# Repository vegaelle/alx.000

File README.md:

# ALX.000

ALX.000 is a compact 18-keys computer numpad, powered by a Seeed XIAO RP2040
micro-controller, and ultra-low-profile Kailh "X" PG1316S switches. It runs QMK,
although support for RMK may come later.

## What’s included here?

This repository contains all needed files for building the keyboard, including parts
list, assembly instructions and useful links.

- The [alx-000.json](alx-000.json) represents the keyboard shape,
produced by [Keyboard-Layout-Editor](https://www.keyboard-layout-editor.com/##@_name=ALX.000&author=vegaelle%3B&@_x:1.5&t=%23ff0000&a:7%3B&=%E2%86%90&_t=%230000ff%3B&=%E2%86%92%3B&@_y:0.5&t=%23000000%0A%23ff0000&a:4%3B&=%0AHome%0A%0A%0A%0A%0A%0A%0A%0A7&=%0A%E2%86%91%0A%0A%0A%0A%0A%0A%0A%0A8&=%0APgUp%0A%0A%0A%0A%0A%0A%0A%0A9&_x:0.5%3B&=%0A,%0A%0A%0A%0A%0A%0A%0A%0A%2F%2F%3B&@=%0A%E2%86%90%0A%0A%0A%0A%0A%0A%0A%0A4&_t=%23000000&a:7&n:true%3B&=5&_t=%23000000%0A%23ff0000&a:4%3B&=%0A%E2%86%92%0A%0A%0A%0A%0A%0A%0A%0A6&_x:0.5%3B&=%0A%2F=%0A%0A%0A%0A%0A%0A%0A%0A*%3B&@=%0AEnd%0A%0A%0A%0A%0A%0A%0A%0A1&=%0A%E2%86%93%0A%0A%0A%0A%0A%0A%0A%0A2&=%0APgDn%0A%0A%0A%0A%0A%0A%0A%0A3&_x:0.5%3B&=%0A%3F%0A%0A%0A%0A%0A%0A%0A%0A-%3B&@=%0ABack%0A%0A%0A%0A%0A%0A%0A%0AEnt&=%0AIns%0A%0A%0A%0A%0A%0A%0A%0A0&=%0ADel%0A%0A%0A%0A%0A%0A%0A%0A.&_x:0.5%3B&=%0A%3F%0A%0A%0A%0A%0A%0A%0A%0A+)
- The [kicad](kicad/) directory contains the Kicad project, representing the PCB. It
uses [Scottokeebs](https://github.com/joe-scotto/scottokeebs/tree/main/Extras/ScottoKicad) libraries and [Mikefive](https://github.com/mikeholscher/zmk-config-mikefive/tree/main/files)’s footprints
- the PG1316 keycaps can be 3D-printed, either with the [blank model](pg1316s_keycap.3mf), or with the OpenSCAD script that allows customization, even with labels, in the [keycaps](keycaps) directory
- The case has been designed in [OnShape](https://cad.onshape.com/documents/826440f605c19707b80cd65a/w/c0d96e8d9f2b88321da9ff87/e/a88972e39d45dd27abd71d1e?renderMode=0&uiState=67a777fa368aed7a59f7b05c). I would have liked to make it in FreeCAD but even in 1.0, it simply wasn’t usable enough.
- The [qmk_firmware/keyoards/alx/000](qmk_firmware/keyboards/alx/000) directory contains
the keyboard definition for QMK, required to build the firmware and edit the keymap.

## Why design a numpad in the first place?

1. Because it’s fun
2. I ultimately want to design my own ergomech keyboard, and this simple project is a
   first step
3. I wanted to try those ultra-thin switches, and it will be a nice way to try those

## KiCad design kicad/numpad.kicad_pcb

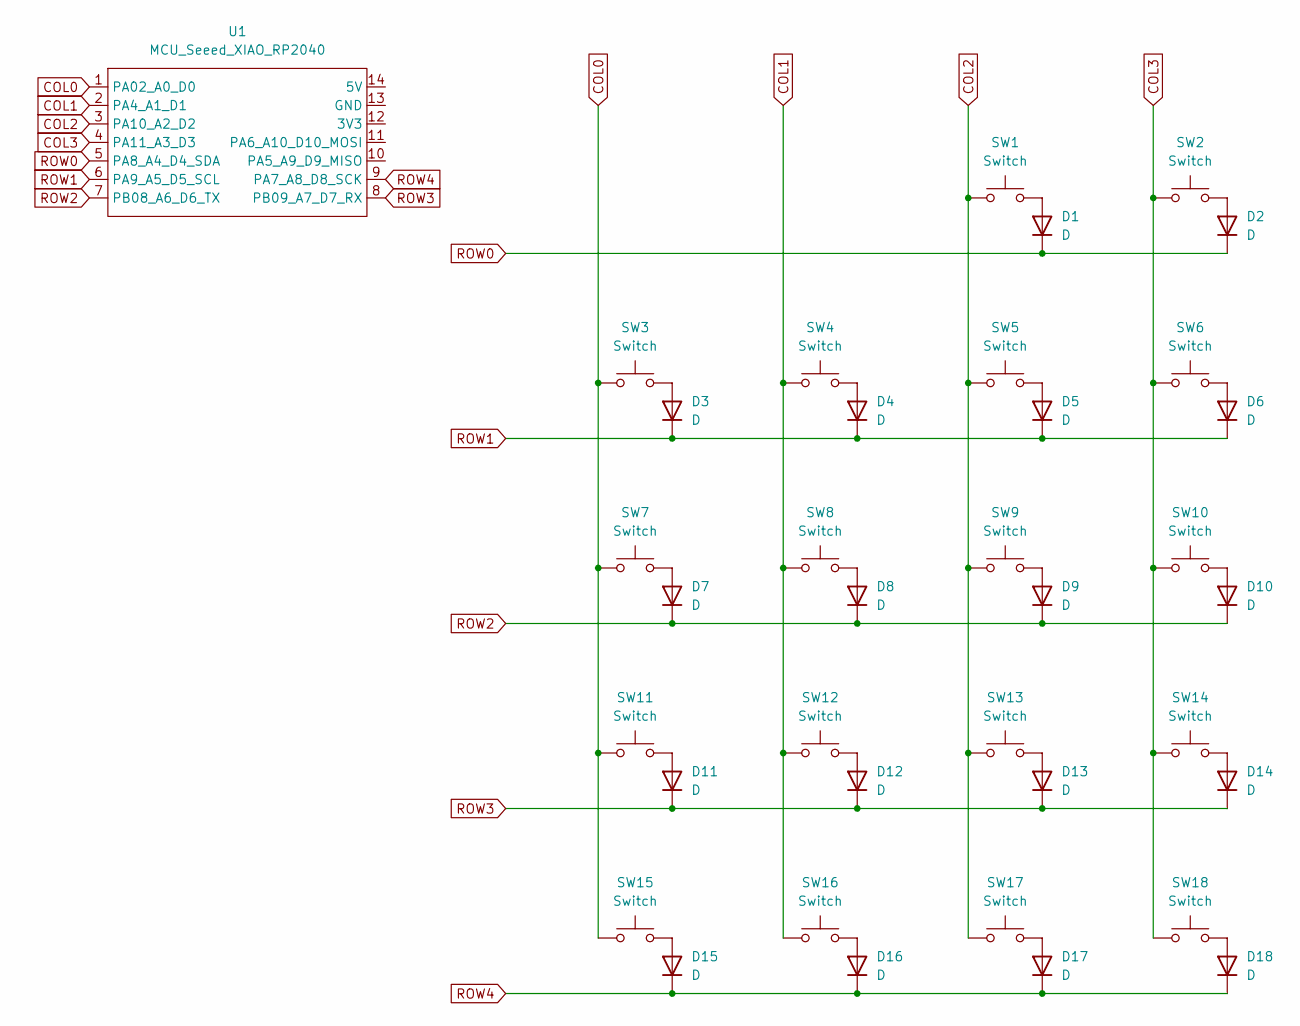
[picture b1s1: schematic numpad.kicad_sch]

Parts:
D1, D2, D3, D4, D5, D6, D7, D8, D9, D10, D11, D12, D13, D14, D15, D16, D17, D18: D; Diode_SOD-123
SW1, SW2, SW3, SW4, SW5, SW6, SW7, SW8, SW9, SW10, SW11, SW12, SW13, SW14, SW15, SW16, SW17, SW18: Switch; CPG1316S01D02_mikeholscher
U1: MCU_Seeed_XIAO_RP2040; Seeed_XIAO_RP2040

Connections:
COL0: SW3.1, SW7.1, SW11.1, SW15.1, U1.1 (PA02_A0_D0)
COL1: SW4.1, SW8.1, SW12.1, SW16.1, U1.2 (PA4_A1_D1)
COL2: SW1.1, SW5.1, SW9.1, SW13.1, SW17.1, U1.3 (PA10_A2_D2)
COL3: SW2.1, SW6.1, SW10.1, SW14.1, SW18.1, U1.4 (PA11_A3_D3)
unnamed: D1.2 (A), SW1.2
unnamed: D2.2 (A), SW2.2
unnamed: D3.2 (A), SW3.2
unnamed: D4.2 (A), SW4.2
unnamed: D5.2 (A), SW5.2
unnamed: D6.2 (A), SW6.2
unnamed: D7.2 (A), SW7.2
unnamed: D8.2 (A), SW8.2
unnamed: D9.2 (A), SW9.2
unnamed: D10.2 (A), SW10.2
unnamed: D11.2 (A), SW11.2
unnamed: D12.2 (A), SW12.2
unnamed: D13.2 (A), SW13.2
unnamed: D14.2 (A), SW14.2
unnamed: D15.2 (A), SW15.2
unnamed: D16.2 (A), SW16.2
unnamed: D17.2 (A), SW17.2
unnamed: D18.2 (A), SW18.2
ROW0: D1.1 (K), D2.1 (K), U1.5 (PA8_A4_D4_SDA)
ROW1: D3.1 (K), D4.1 (K), D5.1 (K), D6.1 (K), U1.6 (PA9_A5_D5_SCL)
ROW2: D7.1 (K), D8.1 (K), D9.1 (K), D10.1 (K), U1.7 (PB08_A6_D6_TX)
ROW3: D11.1 (K), D12.1 (K), D13.1 (K), D14.1 (K), U1.8 (PB09_A7_D7_RX)
ROW4: D15.1 (K), D16.1 (K), D17.1 (K), D18.1 (K), U1.9 (PA7_A8_D8_SCK)

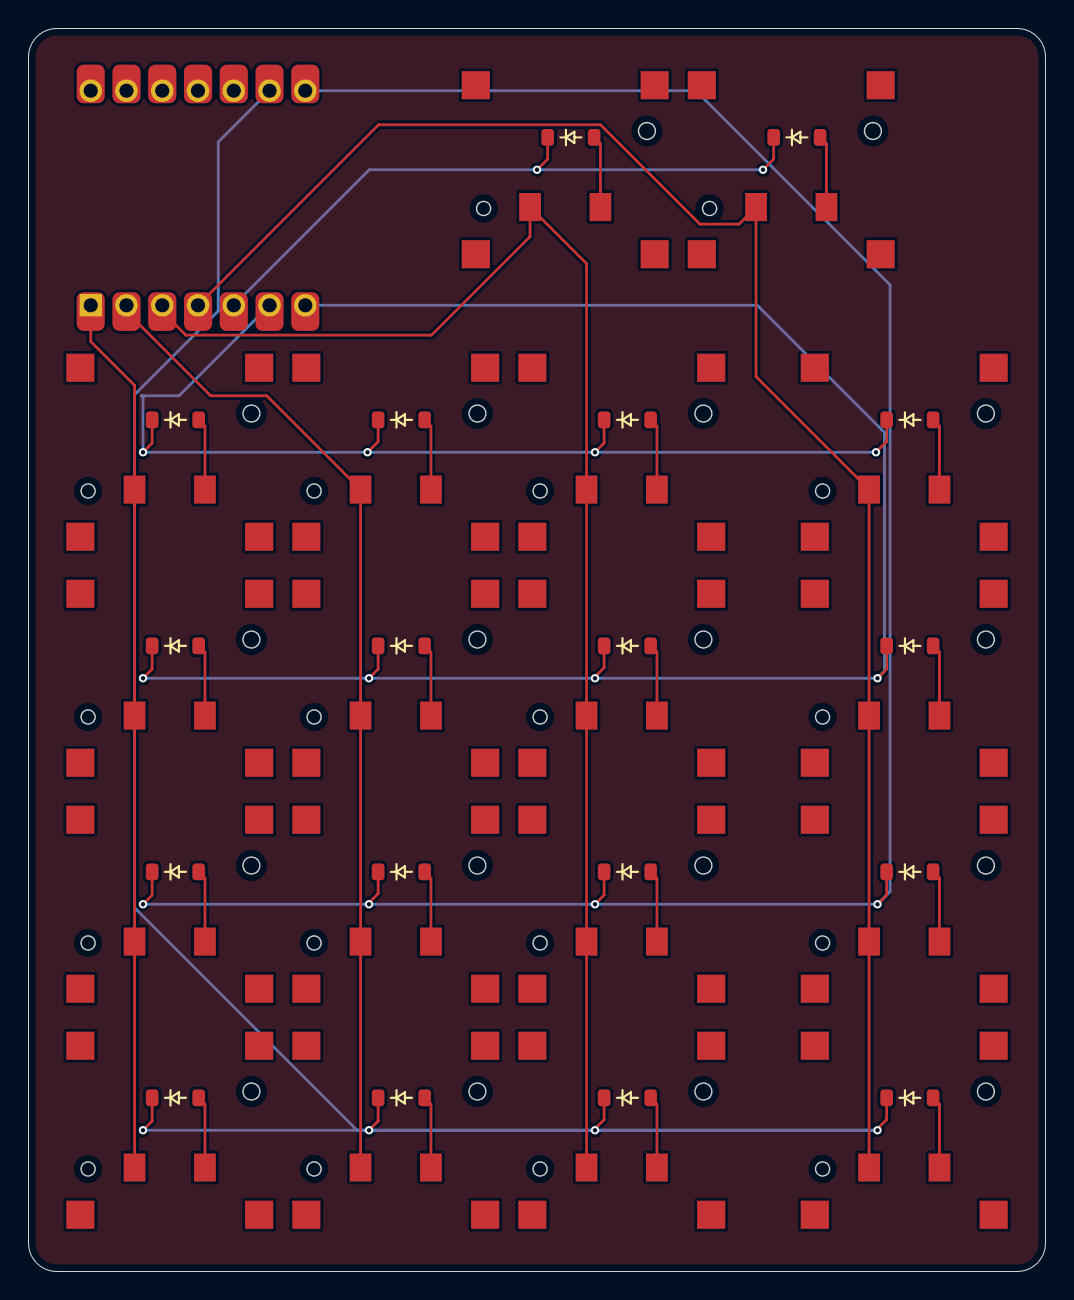
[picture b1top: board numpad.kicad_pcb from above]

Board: 2 copper layers, 72.2 x 88.2 mm, 37 parts (0 on the bottom side), 27 nets.

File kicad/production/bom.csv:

Designator,Footprint,Quantity,Value,LCSC Part #
"D1, D10, D11, D12, D13, D14, D15, D16, D17, D18, D2, D3, D4, D5, D6, D7, D8, D9",Diode_SOD-123,18,D,
"SW1, SW10, SW11, SW12, SW13, SW14, SW15, SW16, SW17, SW18, SW2, SW3, SW4, SW5, SW6, SW7, SW8, SW9",CPG1316S01D02_mikeholscher,18,Switch,
U1,Seeed_XIAO_RP2040,1,MCU_Seeed_XIAO_RP2040,

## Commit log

2025-02-08 Add first version of numpad files
2025-02-08 Fix QMK keyboard definition
2025-02-08 Try to use the RGB LED
2025-02-08 Fix RGB LED usage
2025-02-11 Add keycaps scad script and renders
2025-02-17 [WIP] Keycaps generation script, using lib3mf
2025-02-17 Add to_3mf working version of keycap generator script
